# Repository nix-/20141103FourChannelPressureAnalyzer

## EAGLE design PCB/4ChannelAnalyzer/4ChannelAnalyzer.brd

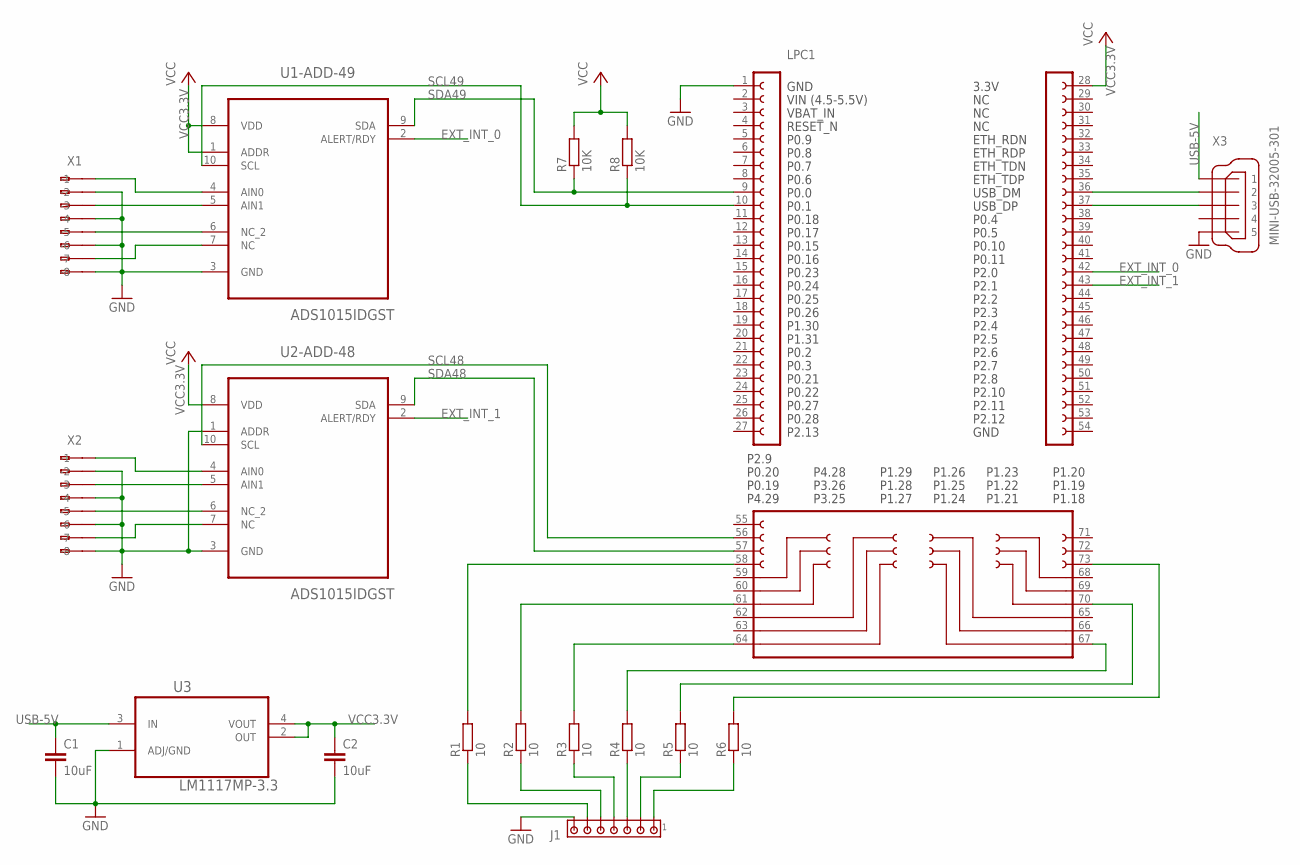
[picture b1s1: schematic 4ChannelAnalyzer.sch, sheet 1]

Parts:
C1, C2: 10uF; C0805
J1: MTA07-100; 10X07MTA
LPC1: LPCXPRESSO_LPC1769
R1, R2, R3, R4, R5, R6: 10; M2012
R7, R8: 10K; M0805
U1-ADD-49, U2-ADD-48: ADS1015IDGST; SOP50P490X110-10N
U3: LM1117MP-3.3; SOT230P696X180-4N
X1, X2: 233-108
X3: MINI-USB-32005-301; 32005-301

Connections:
EXT_INT_0: LPC1.42, U1-ADD-49.2 (ALERT/RDY)
EXT_INT_1: LPC1.43, U2-ADD-48.2 (ALERT/RDY)
GND: C1.2, C2.2, J1.7, LPC1.1, U1-ADD-49.3 (GND), U2-ADD-48.1 (ADDR), U2-ADD-48.3 (GND), U3.1 (ADJ/GND), X1.A2 (-2), X1.A4 (-4), X1.A6 (-6), X1.A8 (-8), X2.A2 (-2), X2.A4 (-4), X2.A6 (-6), X2.A8 (-8), X3.5
unnamed: U1-ADD-49.4 (AIN0), X1.A1 (-1)
unnamed: J1.6, R1.1
unnamed: J1.5, R2.1
unnamed: J1.4, R3.1
unnamed: J1.3, R4.1
unnamed: J1.2, R5.1
unnamed: J1.1, R6.1
unnamed: U1-ADD-49.5 (AIN1), X1.A3 (-3)
unnamed: U2-ADD-48.4 (AIN0), X2.A1 (-1)
unnamed: U2-ADD-48.5 (AIN1), X2.A3 (-3)
unnamed: U2-ADD-48.6 (NC_2), X2.A5 (-5)
unnamed: U2-ADD-48.7 (NC), X2.A7 (-7)
unnamed: U1-ADD-49.6 (NC_2), X1.A5 (-5)
unnamed: U1-ADD-49.7 (NC), X1.A7 (-7)
unnamed: LPC1.36, X3.2
unnamed: LPC1.37, X3.3
unnamed: LPC1.58, R1.2
unnamed: LPC1.61, R2.2
unnamed: LPC1.64, R3.2
unnamed: LPC1.67, R4.2
unnamed: LPC1.70, R5.2
unnamed: LPC1.73, R6.2
SCL48: LPC1.56, U2-ADD-48.10 (SCL)
SCL49: LPC1.10, R8.1, U1-ADD-49.10 (SCL)
SDA48: LPC1.57, U2-ADD-48.9 (SDA)
SDA49: LPC1.9, R7.1, U1-ADD-49.9 (SDA)
USB-5V: C1.1, U3.3 (IN), X3.1
VCC3.3V: C2.1, LPC1.28, R7.2, R8.2, U1-ADD-49.1 (ADDR), U1-ADD-49.8 (VDD), U2-ADD-48.8 (VDD), U3.2 (OUT), U3.4 (VOUT)

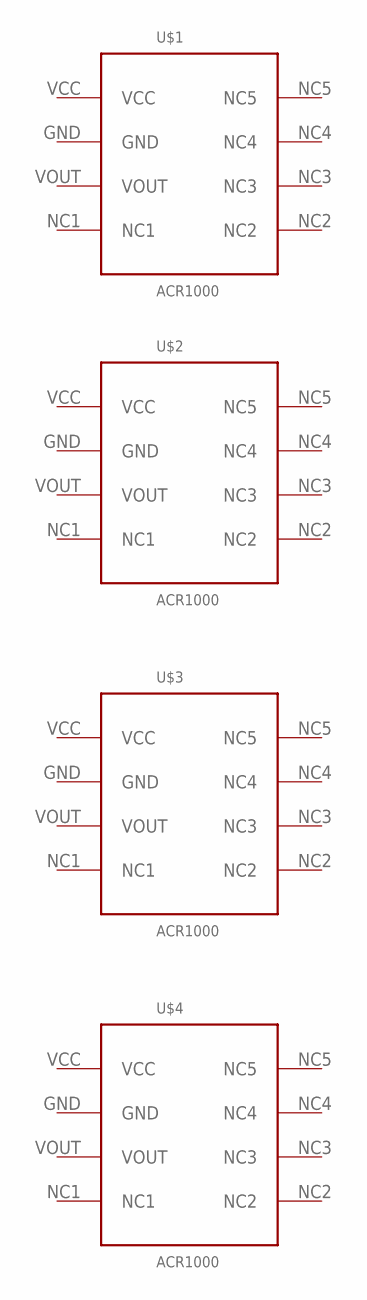
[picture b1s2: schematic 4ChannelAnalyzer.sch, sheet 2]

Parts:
U$1, U$2, U$3, U$4: ACR1000

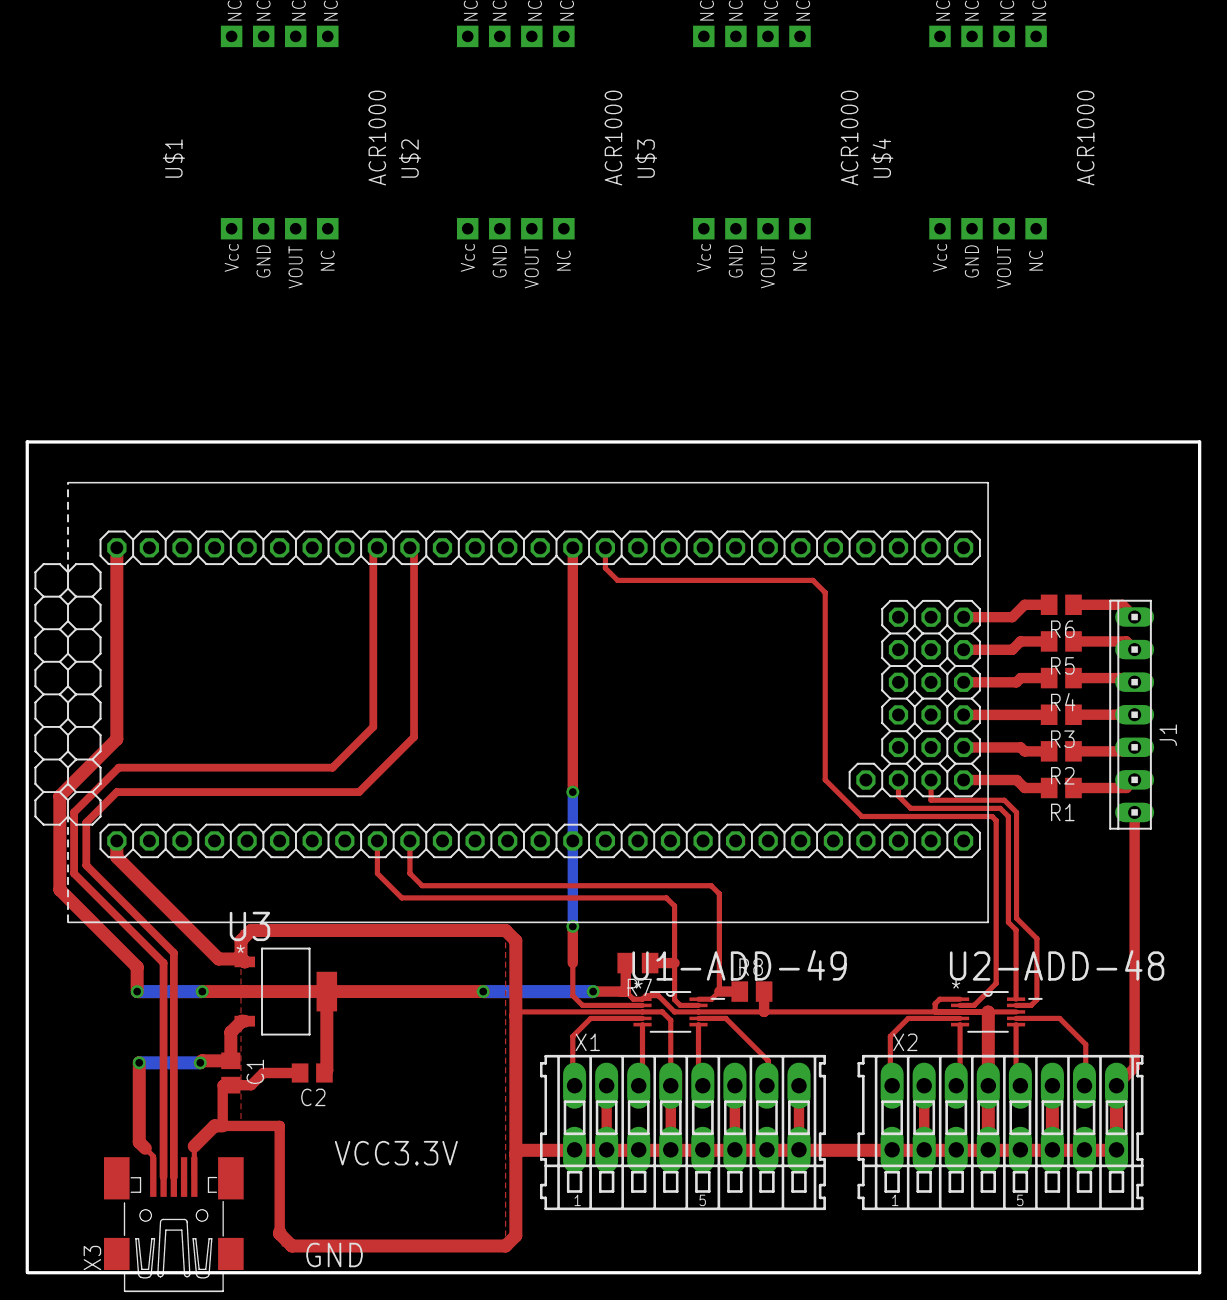
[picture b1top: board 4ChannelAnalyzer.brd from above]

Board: 2 copper layers, 91.4 x 64.8 mm, 22 parts (0 on the bottom side), 31 nets.

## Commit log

2014-11-04 Added LPC1769 board library and pin functionality description.
2014-11-04 Creating empty Eagle project.
2014-11-04 Added ADS1015 (ADC) library to the project.
2014-11-04 Added Linear Voltage Stabilizer LM1117 (3.3V)
2014-11-04 Added components to the PCB design
2014-11-04 Added Data Sheet for pressure sensor module.
2014-11-04 Marking dimension of the PCB board. (Milling line)
2014-11-04 Wiring ADCs with connectors and LED.
2014-11-04 Added LM1117 Linear Voltage Stabilizer
    Added LM1117 Linear Voltage Stabilizer
2014-11-04 Repositioning components in to PCB design
    Repositioning components which are included in to the project
2014-11-04 Commit project file
2014-11-04 adc's ready signal pins / USB connector
    connected adc's ready signal pins to uC and wired USB connector
2014-11-05 Wired LED signals.
2014-11-05 Conected ADC to uC, wired ADC to connector (in PCB)
2014-11-05 Wiring all components (without power supply)
2014-11-07 Reorganize board and added Heat sink for voltage stabilizer.
2014-11-07 Wiring sensors connectors.
2014-11-07 completely wired U2-ADD-48
2014-11-07 Final design of the of the main module PCB
2014-11-07 Created new library ACR1000.lbr
2014-11-07 Added ACR1000 in to circuit and PCB design
    Creating New Sheet for sensors module.
    Added ARC1000 in to design.
2014-11-08 Repositioning one of the PullUp resistors for I2C
